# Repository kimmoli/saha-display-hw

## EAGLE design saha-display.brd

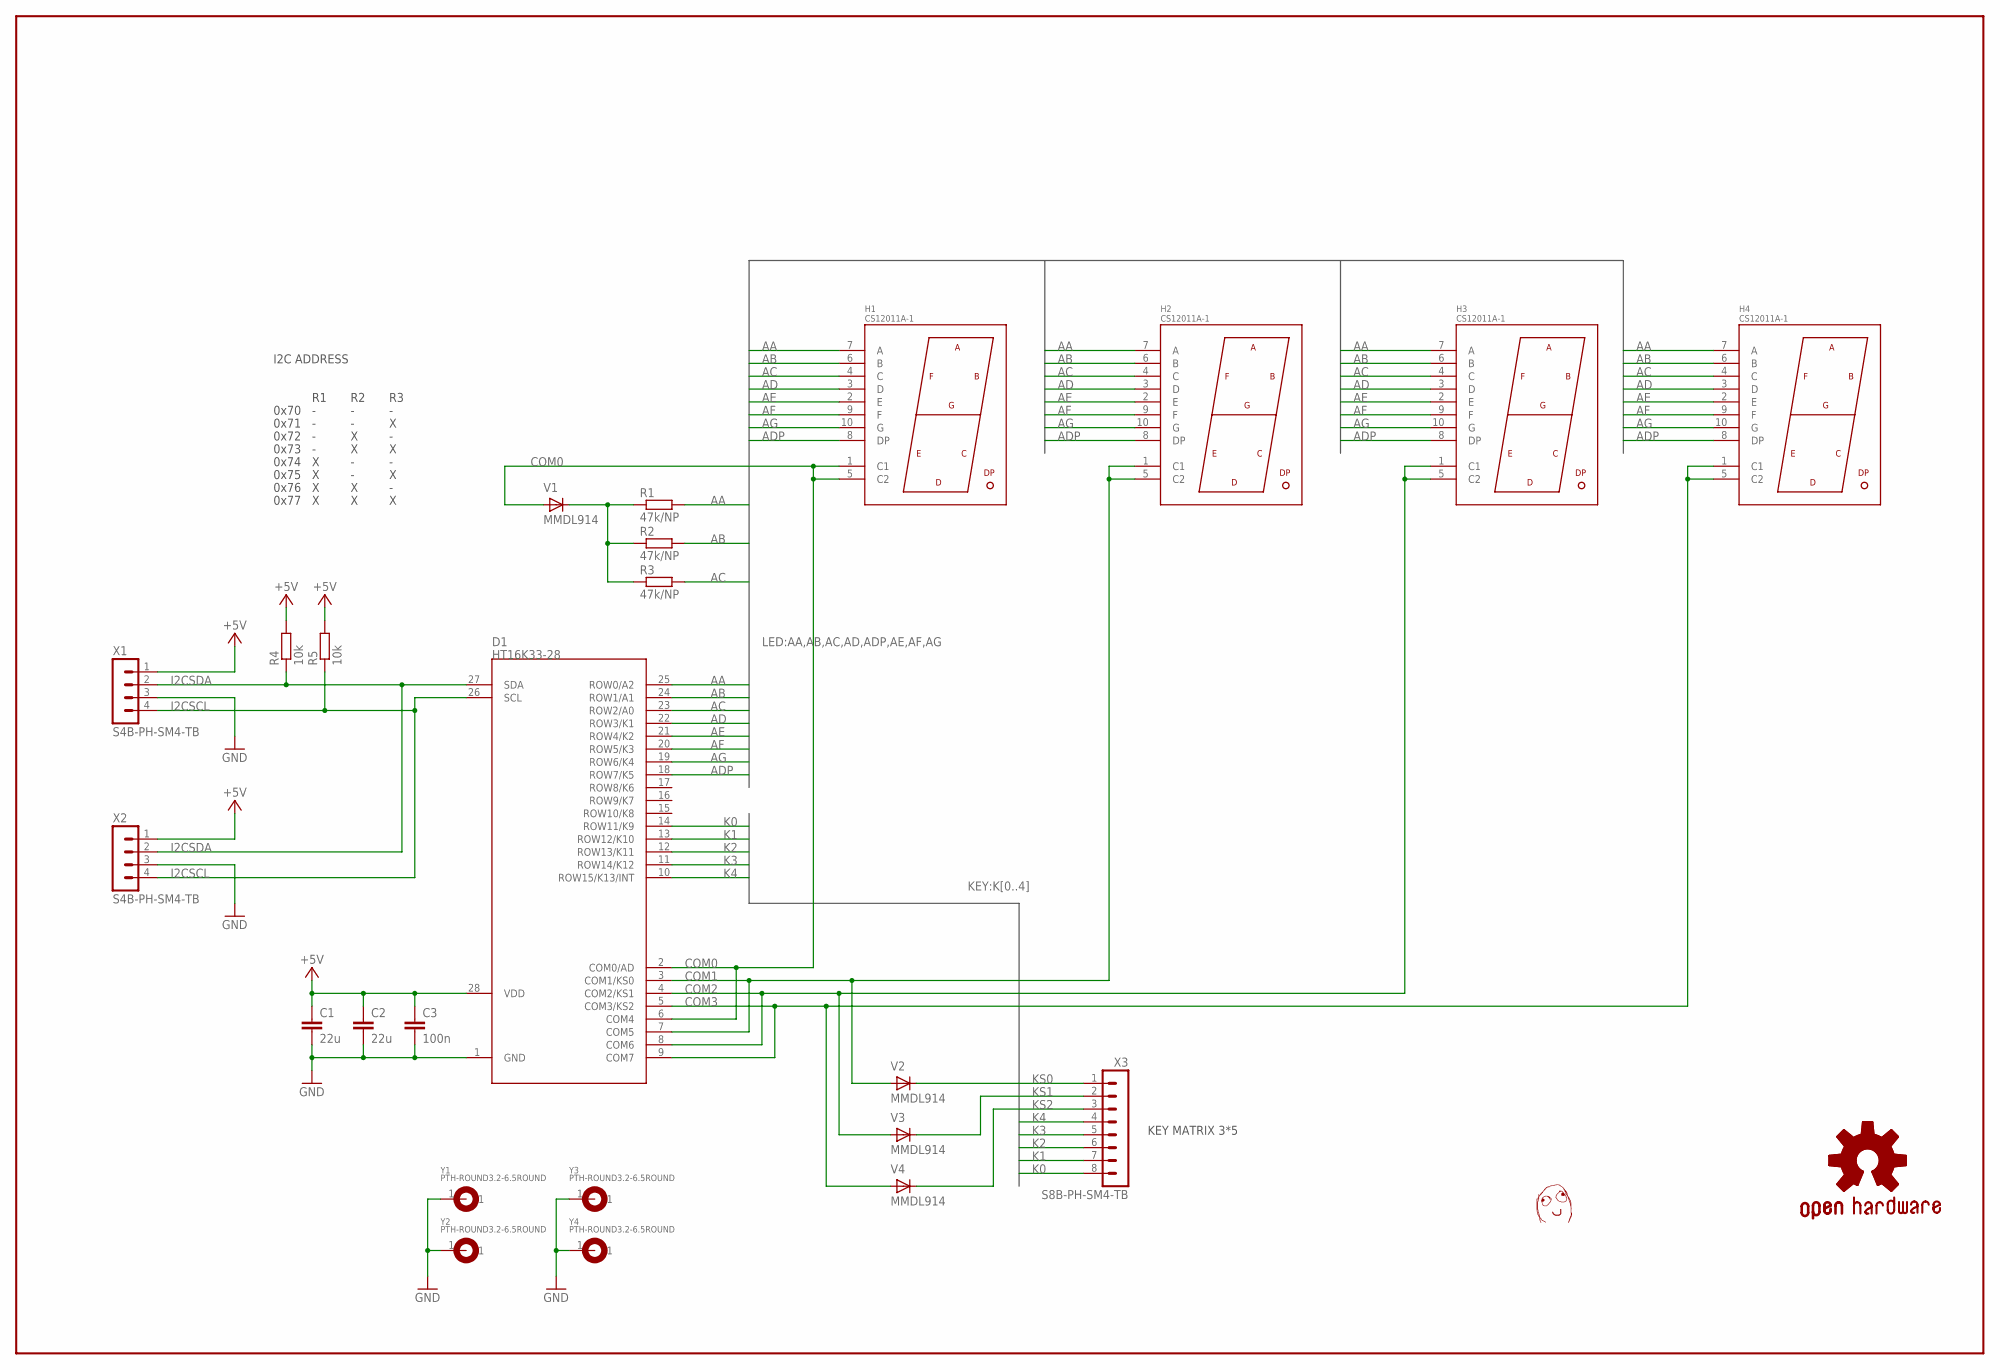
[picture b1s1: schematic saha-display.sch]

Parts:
C1, C2: 22u; C0805
C3: 100n; C0603
D1: HT16K33-28; SOP28-300
H1, H2, H3, H4: CS12011A-1; 7-SEGMENT-1.2INCH
R1, R2, R3: 47k/NP; R0603
R4, R5: 10k; R0603
U$1: DAFUG
V1, V2, V3, V4: MMDL914; SOD-323
X1, X2: S4B-PH-SM4-TB; JST-PH2.0-RA-4
X3: S8B-PH-SM4-TB; JST-PH2.0-RA-8
Y1, Y2, Y3, Y4: PTH-ROUND3.2-6.5ROUND; EKE_PTH-3.2-6.5

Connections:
+5V: C1.1, C2.1, C3.1, D1.28 (VDD), R4.2, R5.2, X1.1, X2.1
AA: D1.25 (ROW0/A2), H1.7 (A), H2.7 (A), H3.7 (A), H4.7 (A), R1.2
AB: D1.24 (ROW1/A1), H1.6 (B), H2.6 (B), H3.6 (B), H4.6 (B), R2.2
AC: D1.23 (ROW2/A0), H1.4 (C), H2.4 (C), H3.4 (C), H4.4 (C), R3.2
AD: D1.22 (ROW3/K1), H1.3 (D), H2.3 (D), H3.3 (D), H4.3 (D)
ADP: D1.18 (ROW7/K5), H1.8 (DP), H2.8 (DP), H3.8 (DP), H4.8 (DP)
AE: D1.21 (ROW4/K2), H1.2 (E), H2.2 (E), H3.2 (E), H4.2 (E)
AF: D1.20 (ROW5/K3), H1.9 (F), H2.9 (F), H3.9 (F), H4.9 (F)
AG: D1.19 (ROW6/K4), H1.10 (G), H2.10 (G), H3.10 (G), H4.10 (G)
COM0: D1.2 (COM0/AD), D1.6 (COM4), H1.1 (C1), H1.5 (C2), V1.A
COM1: D1.3 (COM1/KS0), D1.7 (COM5), H2.1 (C1), H2.5 (C2), V2.A
COM2: D1.4 (COM2/KS1), D1.8 (COM6), H3.1 (C1), H3.5 (C2), V3.A
COM3: D1.5 (COM3/KS2), D1.9 (COM7), H4.1 (C1), H4.5 (C2), V4.A
GND: C1.2, C2.2, C3.2, D1.1 (GND), X1.3, X2.3, Y1.1, Y2.1, Y3.1, Y4.1
I2CSCL: D1.26 (SCL), R5.1, X1.4, X2.4
I2CSDA: D1.27 (SDA), R4.1, X1.2, X2.2
K0: D1.14 (ROW11/K9), X3.8
K1: D1.13 (ROW12/K10), X3.7
K2: D1.12 (ROW13/K11), X3.6
K3: D1.11 (ROW14/K12), X3.5
K4: D1.10 (ROW15/K13/INT), X3.4
KS0: V2.C, X3.1
KS1: V3.C, X3.2
KS2: V4.C, X3.3
unnamed: R1.1, R2.1, R3.1, V1.C

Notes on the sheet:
I2C ADDRESS
0x70
0x71
0x72
0x73
0x74
0x75
0x76
0x77
KEY MATRIX 3*5

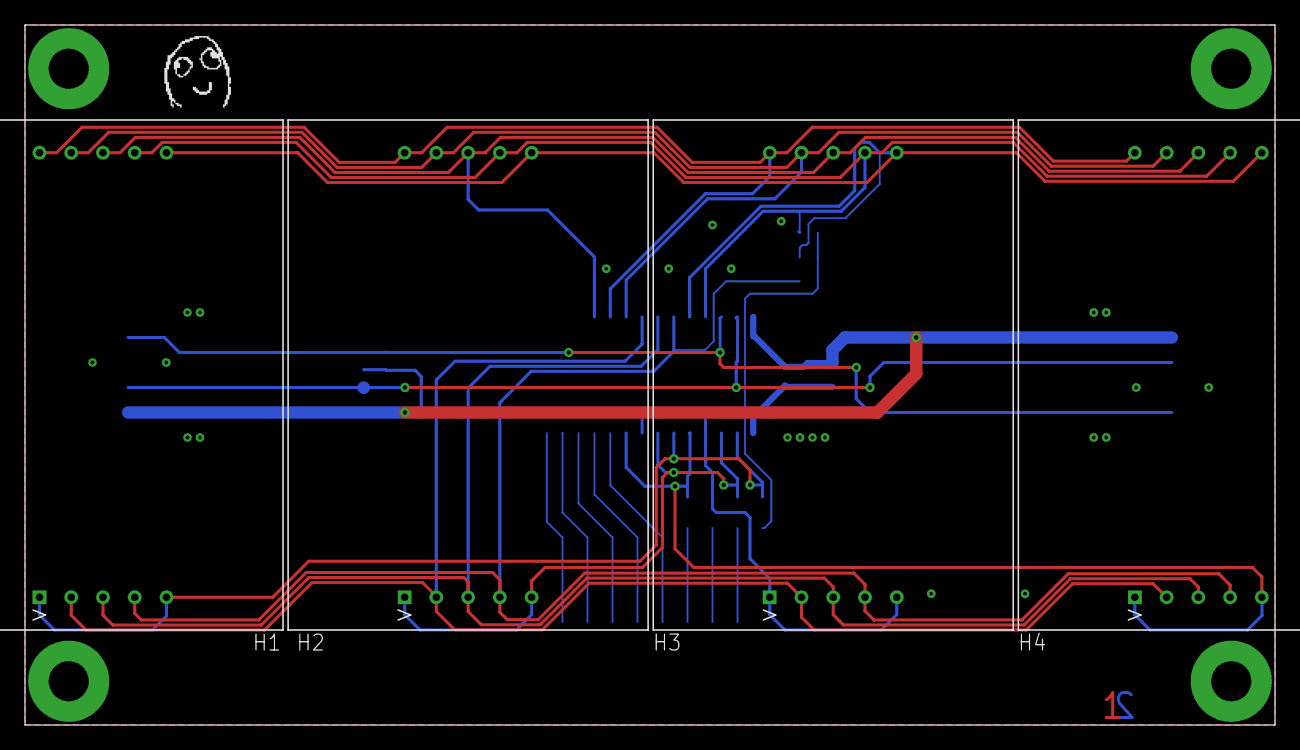
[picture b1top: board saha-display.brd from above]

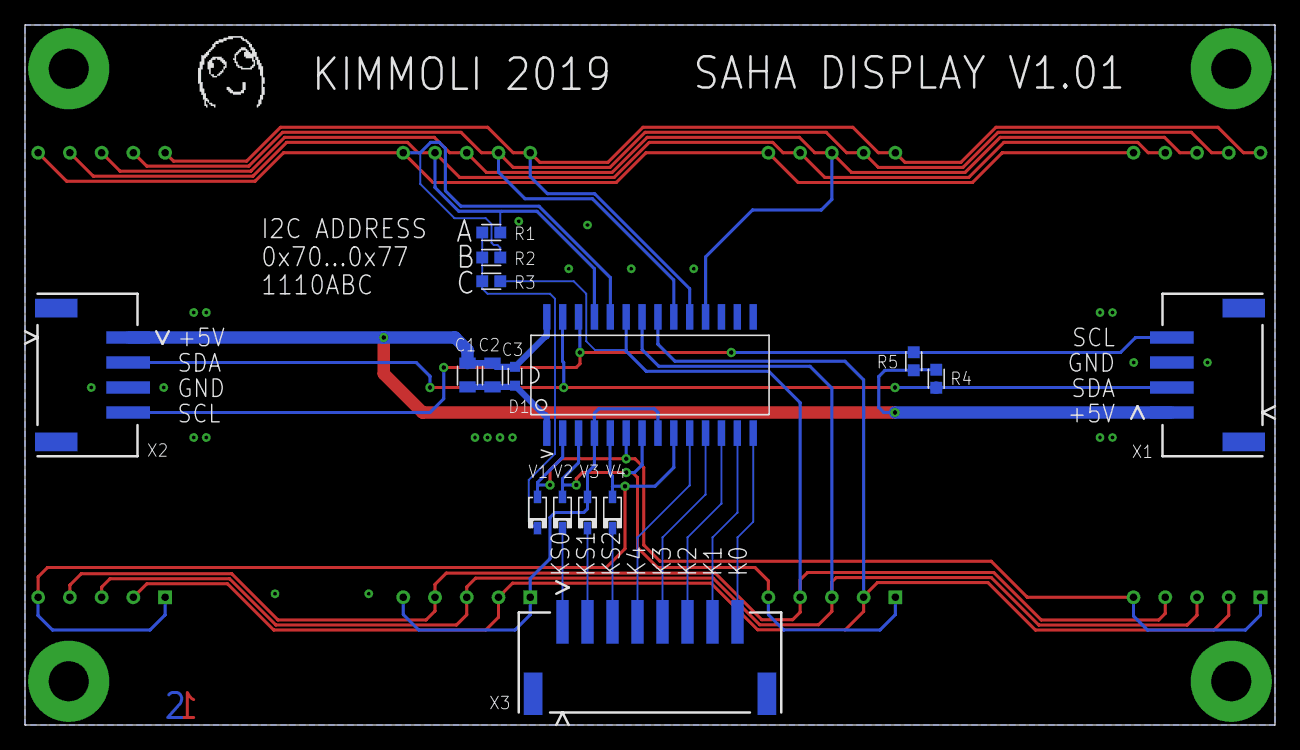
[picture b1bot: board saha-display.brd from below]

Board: 2 copper layers, 100.0 x 56.0 mm, 26 parts (17 on the bottom side), 25 nets.

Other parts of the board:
U$3: DAFUG

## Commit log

2019-05-03 initial
2019-05-03 Layout complete
2019-05-04 add layer window
2019-05-04 fine tuning
2019-05-06 add some doc
2019-09-14 fix layout v1.01
